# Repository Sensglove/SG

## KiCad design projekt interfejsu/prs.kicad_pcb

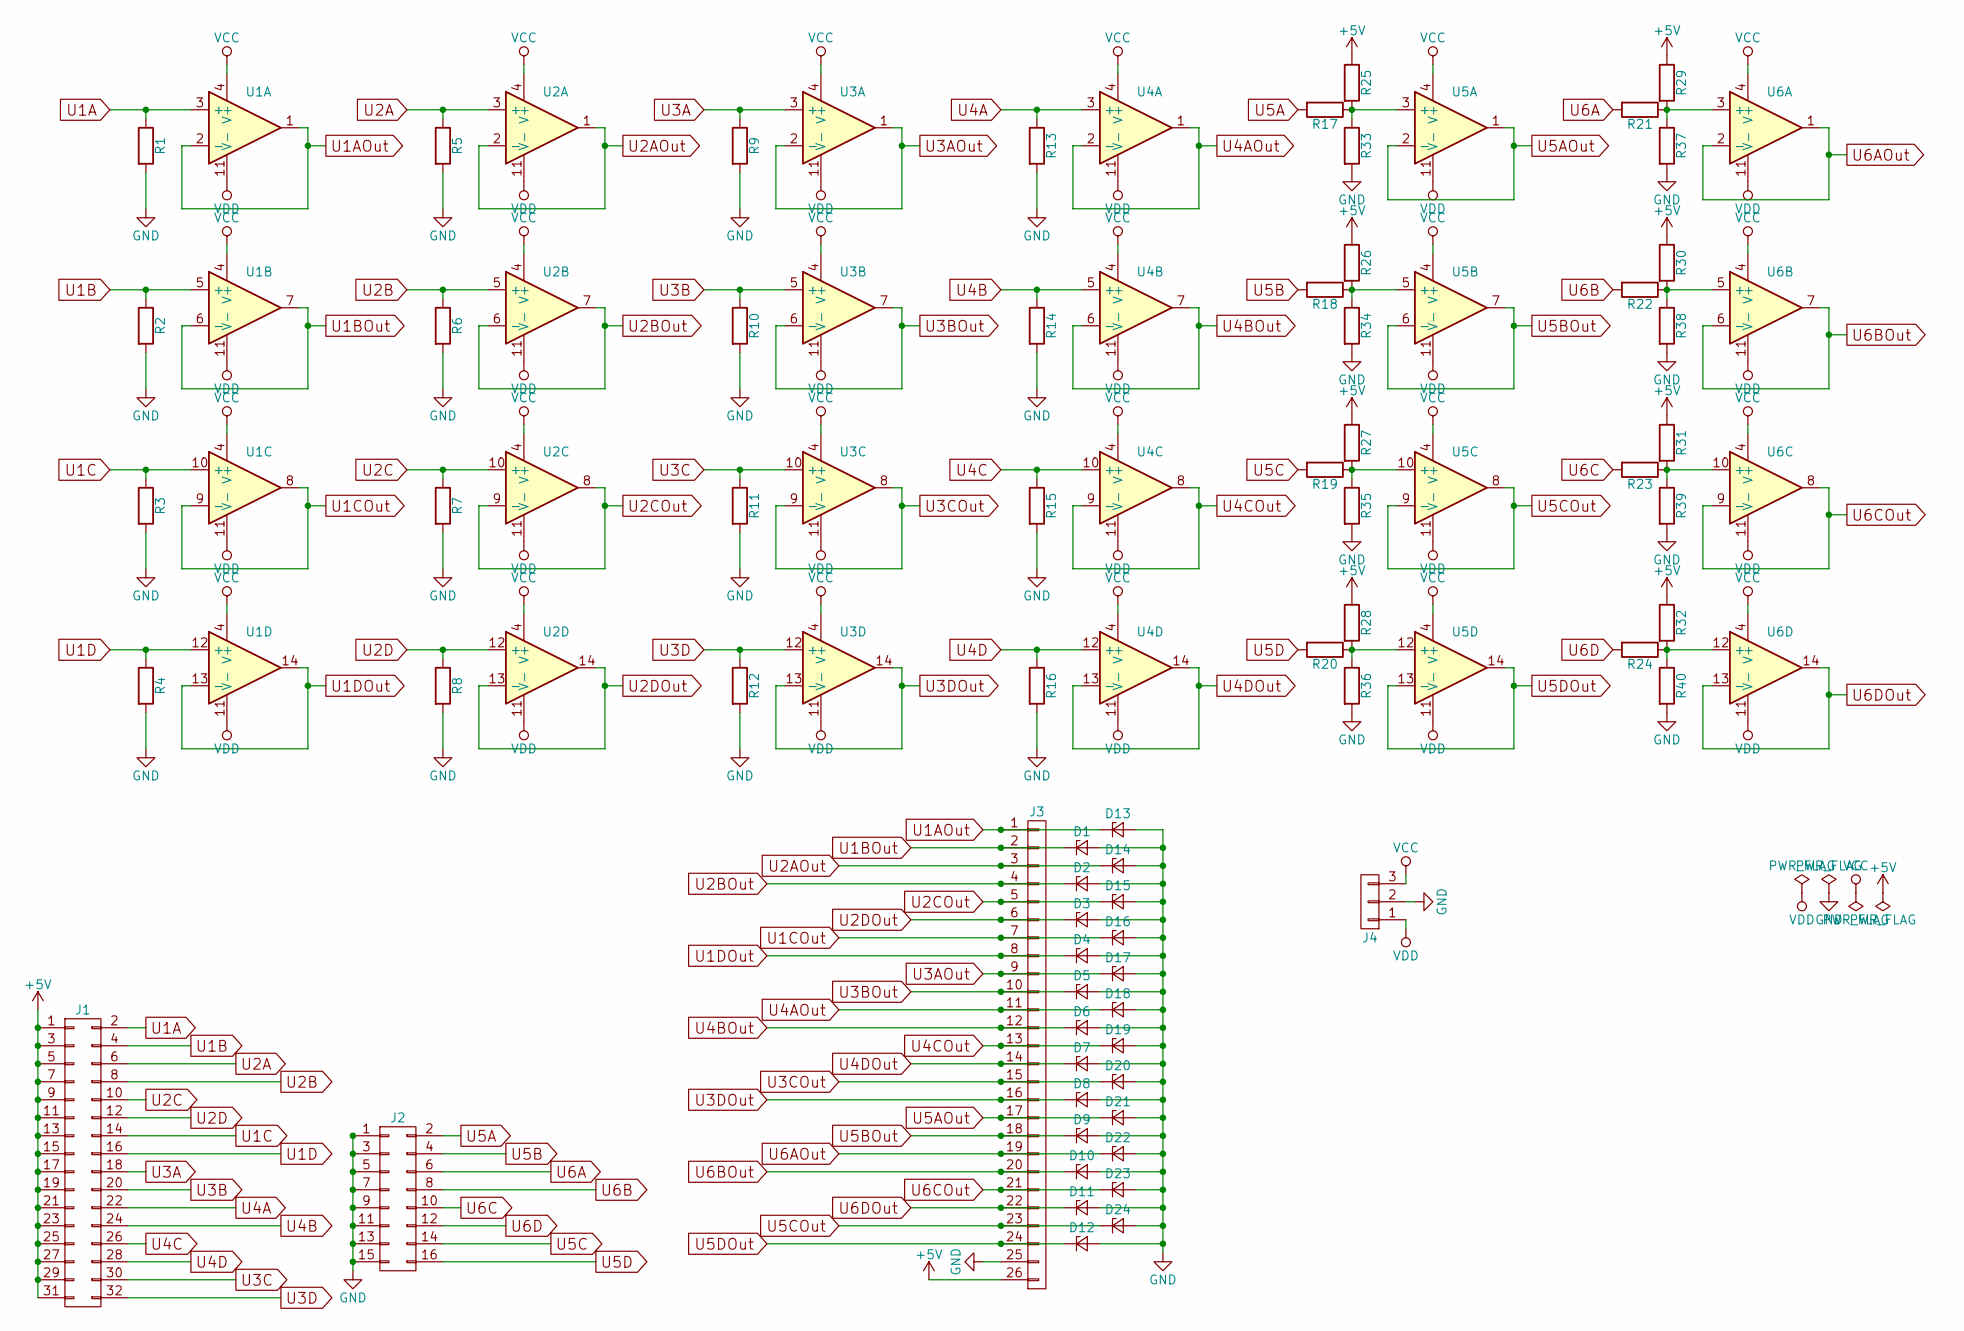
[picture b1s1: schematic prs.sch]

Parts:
D1, D2, D3, D4, D5, D6, D7, D8, D9, D10, D11, D12, D13, D14, D15, D16, D17, D18, D19, D20, D21, D22, D23, D24: D_Zener; D_0805
J1: CONN_02X16; Pin_Header_Straight_2x16_Pitch2.54mm
J2: CONN_02X08; Pin_Header_Straight_2x08_Pitch2.54mm
J3: CONN_01X26; Pin_Header_Straight_1x26_Pitch2.54mm
J4: CONN_01X03; Pin_Header_Straight_1x03_Pitch2.54mm
R1, R2, R3, R4, R5, R6, R7, R8, R9, R10, R11, R12, R13, R14, R15, R16, R25, R26, R27, R28, R29, R30, R31, R32, R33, R34, R35, R36, R37, R38, R39, R40: R_Axial_DIN0207_L6.3mm_D2.5mm_P7.62mm_Horizontal
R17, R18, R19, R20, R21, R22, R23, R24: R_0805_HandSoldering
U1, U2, U3, U4, U5, U6: DIP-14_W7.62mm

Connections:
+5V: J1.1, J1.3, J1.5, J1.7, J1.9, J1.11, J1.13, J1.15, J1.17, J1.19, J1.21, J1.23, J1.25, J1.27, J1.29, J1.31, J3.26, R25.1, R26.1, R27.1, R28.1, R29.1, R30.1, R31.1, R32.1
GND: D1.2 (A), D2.2 (A), D3.2 (A), D4.2 (A), D5.2 (A), D6.2 (A), D7.2 (A), D8.2 (A), D9.2 (A), D10.2 (A), D11.2 (A), D12.2 (A), D13.2 (A), D14.2 (A), D15.2 (A), D16.2 (A), D17.2 (A), D18.2 (A), D19.2 (A), D20.2 (A), D21.2 (A), D22.2 (A), D23.2 (A), D24.2 (A), J2.1, J2.3, J2.5, J2.7, J2.9, J2.11, J2.13, J2.15, J3.25, J4.2, R1.2, R2.2, R3.2, R4.2, R5.2, R6.2, R7.2, R8.2, R9.2, R10.2, R11.2, R12.2, R13.2, R14.2, R15.2, R16.2, R33.2, R34.2, R35.2, R36.2, R37.2, R38.2, R39.2, R40.2
unnamed: R17.1, R25.2, R33.1, U5.3 (+)
unnamed: R18.1, R26.2, R34.1, U5.5 (+)
unnamed: R19.1, R27.2, R35.1, U5.10 (+)
unnamed: R20.1, R28.2, R36.1, U5.12 (+)
unnamed: R21.1, R29.2, R37.1, U6.3 (+)
unnamed: R22.1, R30.2, R38.1, U6.5 (+)
unnamed: R23.1, R31.2, R39.1, U6.10 (+)
unnamed: R24.1, R32.2, R40.1, U6.12 (+)
U1A: J1.2, R1.1, U1.3 (+)
U1AOut: D13.1 (K), J3.1, U1.1, U1.2 (-)
U1B: J1.4, R2.1, U1.5 (+)
U1BOut: D1.1 (K), J3.2, U1.6 (-), U1.7
U1C: J1.14, R3.1, U1.10 (+)
U1COut: D16.1 (K), J3.7, U1.8, U1.9 (-)
U1D: J1.16, R4.1, U1.12 (+)
U1DOut: D4.1 (K), J3.8, U1.13 (-), U1.14
U2A: J1.6, R5.1, U2.3 (+)
U2AOut: D14.1 (K), J3.3, U2.1, U2.2 (-)
U2B: J1.8, R6.1, U2.5 (+)
U2BOut: D2.1 (K), J3.4, U2.6 (-), U2.7
U2C: J1.10, R7.1, U2.10 (+)
U2COut: D15.1 (K), J3.5, U2.8, U2.9 (-)
U2D: J1.12, R8.1, U2.12 (+)
U2DOut: D3.1 (K), J3.6, U2.13 (-), U2.14
U3A: J1.18, R9.1, U3.3 (+)
U3AOut: D17.1 (K), J3.9, U3.1, U3.2 (-)
U3B: J1.20, R10.1, U3.5 (+)
U3BOut: D5.1 (K), J3.10, U3.6 (-), U3.7
U3C: J1.30, R11.1, U3.10 (+)
U3COut: D20.1 (K), J3.15, U3.8, U3.9 (-)
U3D: J1.32, R12.1, U3.12 (+)
U3DOut: D8.1 (K), J3.16, U3.13 (-), U3.14
U4A: J1.22, R13.1, U4.3 (+)
U4AOut: D18.1 (K), J3.11, U4.1, U4.2 (-)
U4B: J1.24, R14.1, U4.5 (+)
U4BOut: D6.1 (K), J3.12, U4.6 (-), U4.7
U4C: J1.26, R15.1, U4.10 (+)
U4COut: D19.1 (K), J3.13, U4.8, U4.9 (-)
U4D: J1.28, R16.1, U4.12 (+)
U4DOut: D7.1 (K), J3.14, U4.13 (-), U4.14
U5A: J2.2, R17.2
U5AOut: D21.1 (K), J3.17, U5.1, U5.2 (-)
U5B: J2.4, R18.2
U5BOut: D9.1 (K), J3.18, U5.6 (-), U5.7
U5C: J2.14, R19.2
U5COut: D24.1 (K), J3.23, U5.8, U5.9 (-)
U5D: J2.16, R20.2
U5DOut: D12.1 (K), J3.24, U5.13 (-), U5.14
U6A: J2.6, R21.2
U6AOut: D22.1 (K), J3.19, U6.1, U6.2 (-)
U6B: J2.8, R22.2
U6BOut: D10.1 (K), J3.20, U6.6 (-), U6.7
U6C: J2.10, R23.2
U6COut: D23.1 (K), J3.21, U6.8, U6.9 (-)
U6D: J2.12, R24.2
U6DOut: D11.1 (K), J3.22, U6.13 (-), U6.14
VCC: J4.3, U1.4 (V+), U2.4 (V+), U3.4 (V+), U4.4 (V+), U5.4 (V+), U6.4 (V+)
VDD: J4.1, U1.11 (V-), U2.11 (V-), U3.11 (V-), U4.11 (V-), U5.11 (V-), U6.11 (V-)

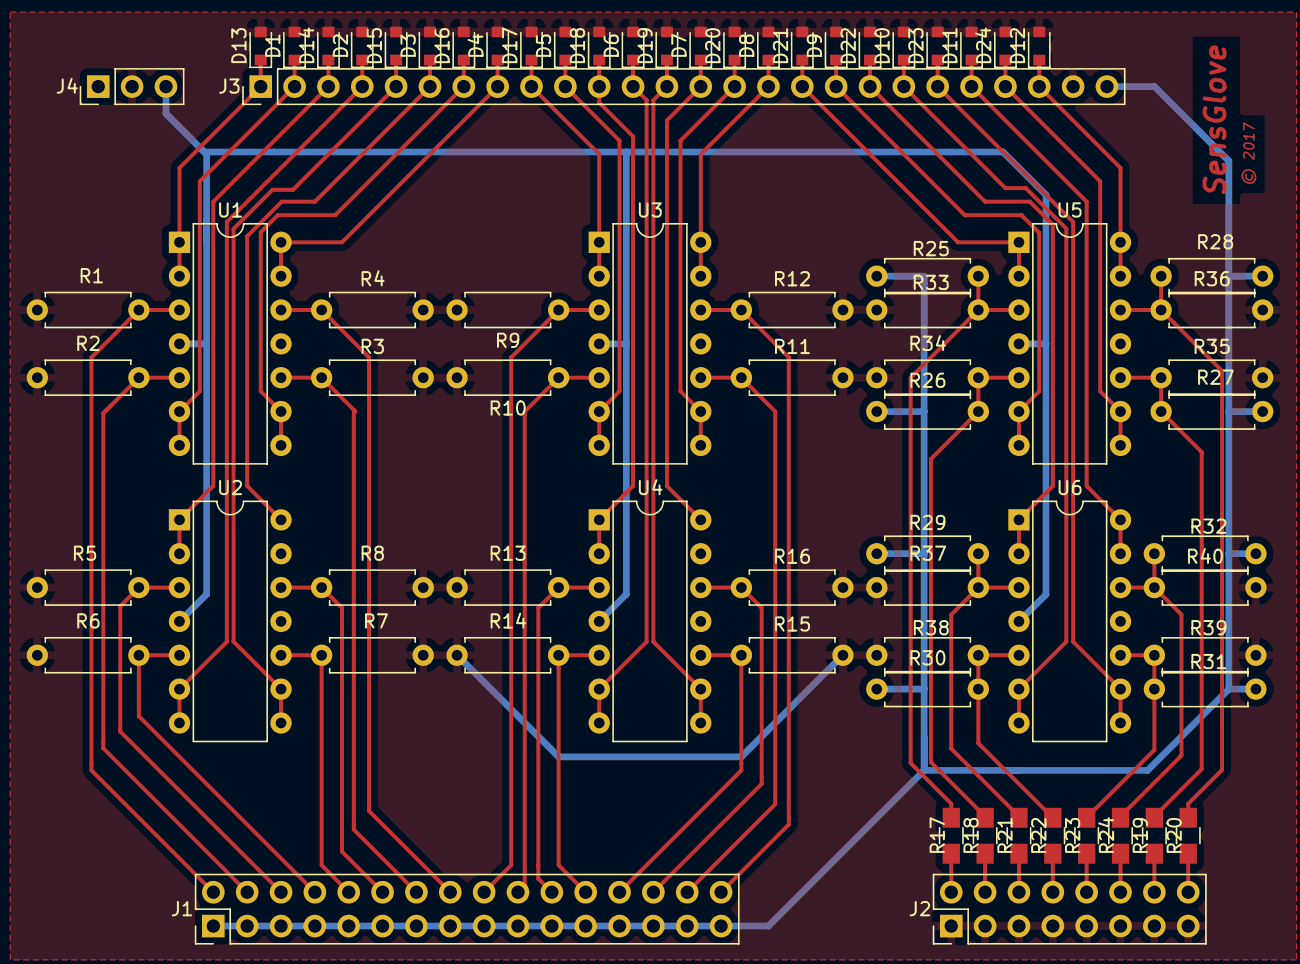
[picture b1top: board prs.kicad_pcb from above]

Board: 2 copper layers, 74 parts (0 on the bottom side), 60 nets.

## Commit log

2017-03-27 Set theme jekyll-theme-minimal
2017-03-27 Test
2017-03-27 oddane zadania
2017-03-27 Test2
2017-03-27 Nowa linia
2017-03-27 just a little change
2017-03-27 Test3
2017-03-29 Materialy bio-pro 1
2017-03-29 Materialy do bio-pro 2
2017-03-29 Materialy z projektu bio-pro od p Arenta
2017-03-31 wersja z eportalu
2017-03-31 teścik
2017-03-31 dod. rozdział
2017-03-31 gosia
2017-04-01 adding section
2017-04-01 dodatkowy chapter
2017-04-01 założenia co do programu
2017-04-01 dodanie założeń interfejsu
2017-04-02 dodany obrazek dawida bez UML na razie
2017-04-02 rozw.
2017-04-02 Dokumenty dostarczone przez dra Wolczowskiego
2017-04-02 Baza danych, wizualizaja, rekawiczka
2017-04-02 Baza danych, wizualizacja, rekawiczka
2017-04-02 Literowki w rekawiczce i czas w wizualizacji
2017-04-02 Bazy danych: schemat, podzial zadan i dadanie funkcji
2017-04-02 obrazek
2017-04-02 ze schematem programu
2017-04-02 Literowki, cena rekawiczki
2017-04-02 literówki
2017-04-02 Znowu literowka
2017-04-02 Montaz
2017-04-02 dodaję znów
2017-04-02 czesciowe zmiany
2017-04-02 wady+zalety
2017-04-03 Usuniecie
2017-04-03 wersja do wstawienia na eportal
2017-04-03 Drobne zmiany
2017-04-03 wersja ostateczna
2017-05-14 wszystko
2017-05-14 program
2017-05-14 makefile tez dziala
2017-05-14 "+socket"
2017-05-14 z socketem ktory nie dziala
2017-05-15 socket oczywiscie nie dziala
2017-05-22 aktualna wersja v0.2
2017-05-22 Skrypt przenoszacy plik do bazy danych
2017-05-22 Poprawiony skrypt do bazy danych
2017-05-22 script version v.0.1.3
2017-05-22 Dodana dokumentacja
2017-06-04 Rename main.tex to raport_ewaluacja
2017-06-04 Rename raport_ewaluacja to raport_ewaluacja.tex
2017-06-04 zmiana do programu z akwizycją danych
2017-06-04 drobne poprawki
2017-06-04 Ewaluacja interfejsu sprzętowego
2017-06-05 Rekawiczka, baza danych i wizualizacja
2017-06-05 dokumentacja doxygen cd.
2017-06-05 Uporzadkowanie dokumentacji
2017-06-09 integracja v.0.4
2017-06-09 suma kontrolna włączona
2017-06-11 interfejs sprzętowy
2017-06-18 z niepełnym doxygenem
2017-06-18 Skrypty Beaty wyszukujace po nazwie i dacie pliki w bazie danych
2017-06-18 Dopracowanie dokumentacji.
2017-06-18 poprawione sprawdzanie dannych
2017-06-18 strona internetowa
2017-06-18 Literówki poprawione
2017-06-19 makefile
2017-06-19 Poprawienie dokumentacji v03
2017-06-19 Sprawozdanie dla dr Wolczowskiego
2017-06-19 poprawki strony internetowej
2017-06-20 Interfejs sprzętowy i oprogramowanie STM
2017-06-20 dokumentacja interfejs sprzętowy
2017-06-20 Folder dokumentacja v04, zdjecia stanowiska
2017-06-20 Aplikacja do akwizycji w wersji z dzisiejszych zajec
2017-06-21 Dokumentacja
2017-06-21 Raport koncowy
2017-06-21 Kod aplikacji wizualizujacej
2017-06-21 Dokumentacja koncowa - dokonczenie
2017-06-21 Dokumentacja koncowa - zakladka 3

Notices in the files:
projekt interfejsu/prs.kicad_pcb:
© 2017
